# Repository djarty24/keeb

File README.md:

# Keeb Journal
Hack Club Keeb custom keyboard.

## Table of Contents
* [6/8](#68)

## 6/8
Just found out about Hack Club Keeb! I wanted to get started with this challenge.

### Planning Your Keyboard
I first read through the [Planning Your Keyboard](https://keeb.hackclub.com/docs/planning/) section in the docs and started brainstorming what I wanted my keyboard to look like. After doing some research, I've decided on a 75% layout for my Mac. I want it to look pretty standard, like this image:

The personalization will be through the keycaps! I'll also add fun illustrations on the PCB silkscreen. I'm thinking of designing my own Monet themed keycaps or purchasing custom ones off of Etsy like the following:

As for the case, I want it to have slight borders around everything and larger borders to separate the arrow keys and function row like the first image displayed.

```
Esc   F1 F2 F3 F4   F5 F6 F7 F8   F9 F10 F11 F12   Power

`  1  2  3  4  5  6  7  8  9  0  -  =   Backspace     Home
Tab Q  W  E  R  T  Y  U  I  O  P  [  ]   \          PgUp
Caps A  S  D  F  G  H  J  K  L  ;  '   Return       PgDn
Shift Z  X  C  V  B  N  M  ,  .  /   Shift   ↑      End
Ctrl Opt Cmd        Space        Cmd Opt     ← ↓ →
```

Design Time: ~90 min

### Designing the PCB (day 1)
Next, I moved on to the [Desighing the PCB](https://keeb.hackclub.com/docs/pcb-design/) section in the docs.

I've decided on linear switches since they seem to be the quietest and best for wrist health.

Initially I was pretty confused with how to even get started. So I headed over to YouTube and watched a tutorial by [Joe Scotto](https://www.youtube.com/watch?v=7LyziNdFlew) that explained direct vs. matrix wiring. Looking at my reference image, my keyboard needs 15 columns and 6 rows, which means my microcontroller needs at least 21 pins. This fits perfectly within the Raspberry Pi Pico's 26 GPIO pins!

Now, it was time to open up KiCAD and get started.

In the tutorial, it said I would need stabilizers for keys larger than 2u. So what I did next was identify the size of each key. Most keys were 1u, however some exceptions:

Tab: 1.5u
Caps Lock: 1.75u
Left Shift: 2.25u
Right Shift: 1.75u
Backslash: 1.5u
Return: 2.25u
Backspace: 2u
Space: 6.25u
Ctrl/Opt/Cmd/Right Cmd/1.25u

My eyes hurt really bad after squinting over the reference image but I believe this is right. So, the only keys that I need stabilizers for are Left Shift, Return, Backspace, and Space.

Then I created one row of keys.

## 6/9

Today, I continued working on the PCB. I finished up adding all of the key-diode units and orienting them to match my physical keyboard inspo. Although it isn't perfectly aligned it should be good enough to move on to the next step. Here's what my matrix looked like:

Next, I added in the Pico and added labels to its GPIO pins. I also added the stabilizers and 5 mounting holes as well.

Now, it was time to move on to the next step!

### Designing the PCB (day 2)

THIS TOOK ME 8 HOURS. I don't have many screenshots since I was pretty locked in but I had to manually orient every single switch-diode unit to match the exact layout I wanted. The grid system in KiCad is pretty bad, so I calculated all of the X-Y coordinates of all 81 keys using a formula I made on Desmos and positioned them accordingly. Then, I placed the diodes and routed all of my traces. This is what it looks like now:

The orientation of stuff is a little ugly but I'm not too picky about how it will look as long as it functions. In the future I will most probably remake this with a different MCU that's more compact than the Pico. This is what the 3d view looks like:

I went to GrabCAD and downloaded some 3D models of the Cherry MX keycaps and switches that were 1u. However, I got tired of adding them all in because I couldn't find a way to globally update their footprints to link to the model, so I added enough to just get an idea of what it would look like. I also added in a 1.5u stabilizer to test how that would look.

Final step for this part was running the Design Rules Checker (DRC) to make sure everything was good. I cleaned up some connections, ran the DRC again, and the PCB was ready to go! I also committed and pushed all of this to GitHub.

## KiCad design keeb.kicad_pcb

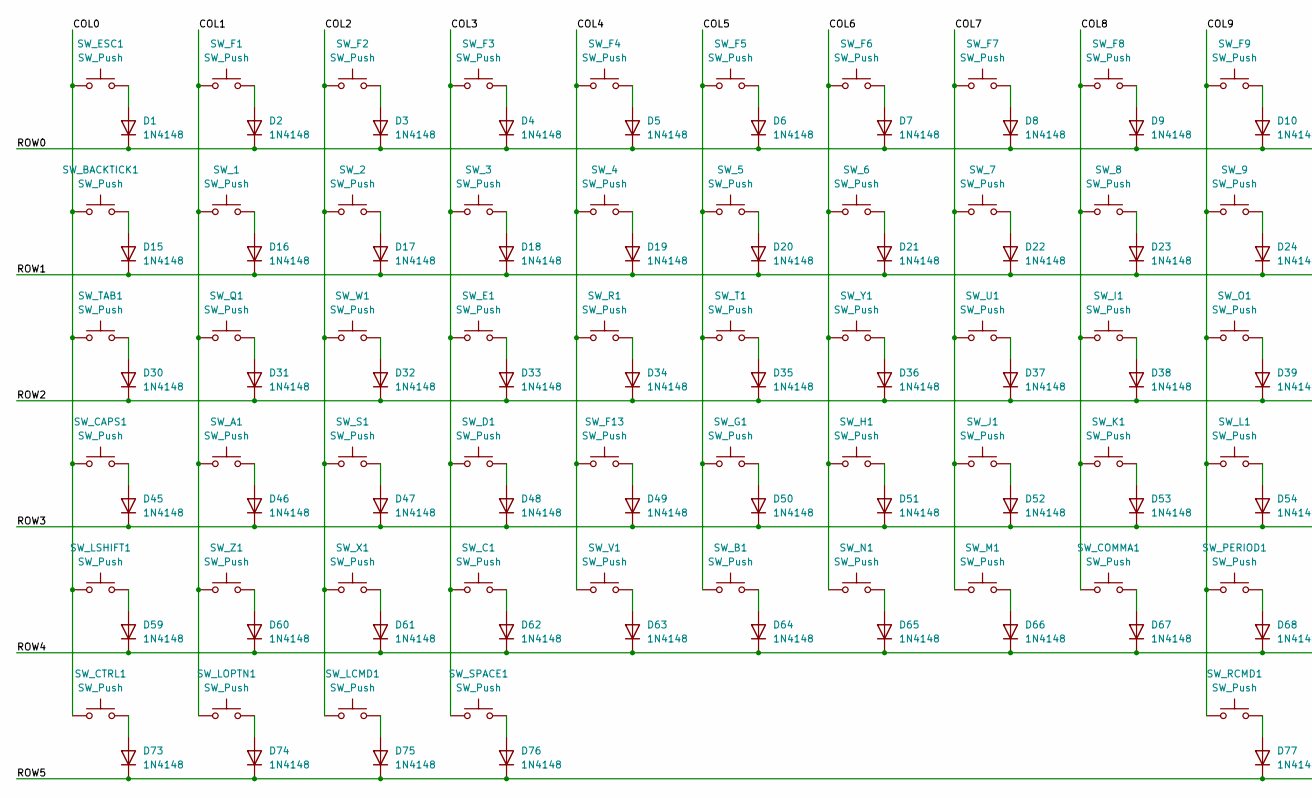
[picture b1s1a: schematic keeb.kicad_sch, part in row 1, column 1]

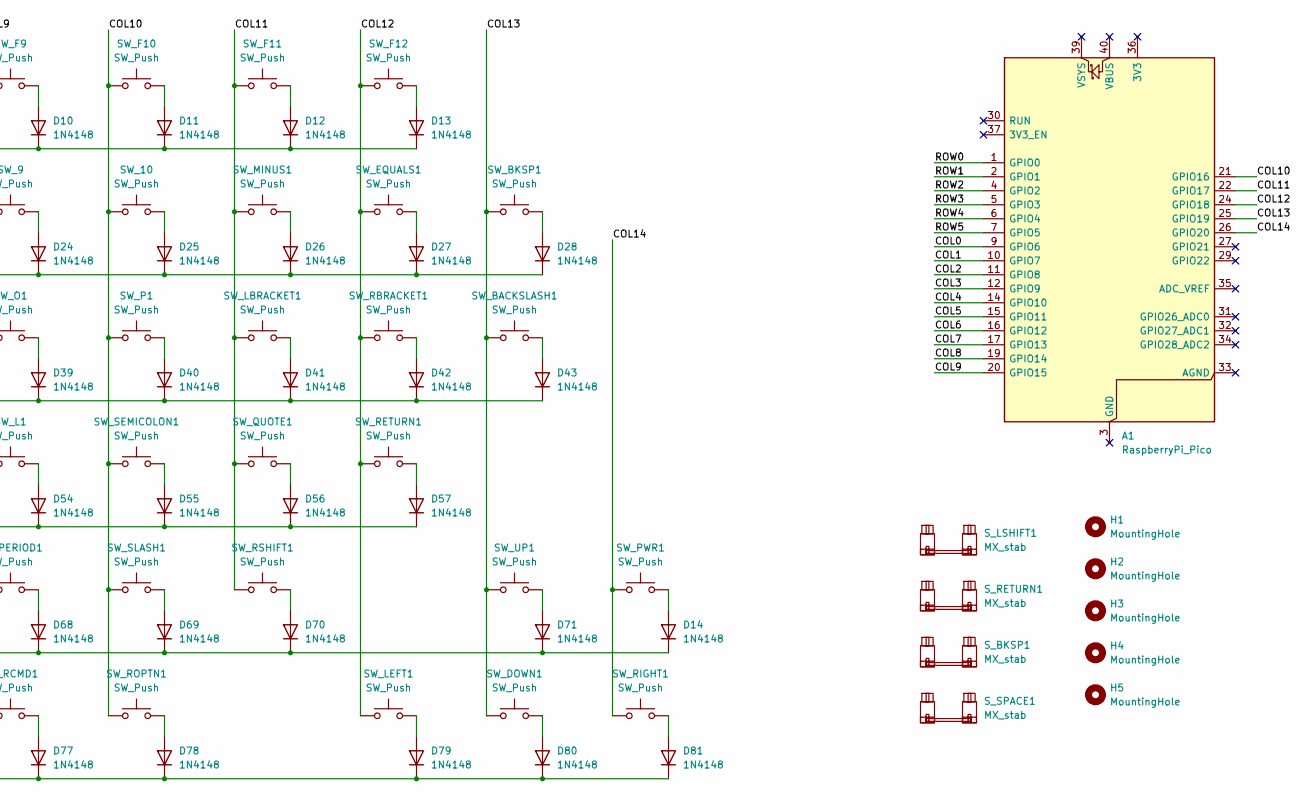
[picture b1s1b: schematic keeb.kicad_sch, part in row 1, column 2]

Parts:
A1: RaspberryPi_Pico; RaspberryPi_Pico_Common_THT
D1, D2, D3, D4, D5, D6, D7, D8, D9, D10, D11, D12, D13, D14, D15, D16, D17, D18, D19, D20, D21, D22, D23, D24, D25, D26, D27, D28, D30, D31, D32, D33, D34, D35, D36, D37, D38, D39, D40, D41, D42, D43, D45, D46, D47, D48, D49, D50, D51, D52, D53, D54, D55, D56, D57, D59, D60, D61, D62, D63, D64, D65, D66, D67, D68, D69, D70, D71, D73, D74, D75, D76, D77, D78, D79, D80, D81: 1N4148; D_DO-35_SOD27_P7.62mm_Horizontal
H1, H2, H3, H4, H5: MountingHole; MountingHole_2.2mm_M2
SW_1, SW_2, SW_3, SW_4, SW_5, SW_6, SW_7, SW_8, SW_9, SW_10: SW_Push; SW_MX_1u
SW_A1: SW_Push; SW_MX_1u
SW_B1: SW_Push; SW_MX_1u
SW_BACKSLASH1: SW_Push; SW_MX_1u
SW_BACKTICK1: SW_Push; SW_MX_1u
SW_BKSP1: SW_Push; SW_MX_1u
SW_C1: SW_Push; SW_MX_1u
SW_CAPS1: SW_Push; SW_MX_1u
SW_COMMA1: SW_Push; SW_MX_1u
SW_CTRL1: SW_Push; SW_MX_1u
SW_D1: SW_Push; SW_MX_1u
SW_DOWN1: SW_Push; SW_MX_1u
SW_E1: SW_Push; SW_MX_1u
SW_EQUALS1: SW_Push; SW_MX_1u
SW_ESC1: SW_Push; SW_MX_1u
SW_F1, SW_F2, SW_F3, SW_F4, SW_F5, SW_F6, SW_F7, SW_F8, SW_F9, SW_F10, SW_F11, SW_F12, SW_F13: SW_Push; SW_MX_1u
SW_G1: SW_Push; SW_MX_1u
SW_H1: SW_Push; SW_MX_1u
SW_I1: SW_Push; SW_MX_1u
SW_J1: SW_Push; SW_MX_1u
SW_K1: SW_Push; SW_MX_1u
SW_L1: SW_Push; SW_MX_1u
SW_LBRACKET1: SW_Push; SW_MX_1u
SW_LCMD1: SW_Push; SW_MX_1u
SW_LEFT1: SW_Push; SW_MX_1u
SW_LOPTN1: SW_Push; SW_MX_1u
SW_LSHIFT1: SW_Push; SW_MX_1u
SW_M1: SW_Push; SW_MX_1u
SW_MINUS1: SW_Push; SW_MX_1u
SW_N1: SW_Push; SW_MX_1u
SW_O1: SW_Push; SW_MX_1u
SW_P1: SW_Push; SW_MX_1u
SW_PERIOD1: SW_Push; SW_MX_1u
SW_PWR1: SW_Push; SW_MX_1u
SW_Q1: SW_Push; SW_MX_1u
SW_QUOTE1: SW_Push; SW_MX_1u
SW_R1: SW_Push; SW_MX_1u
SW_RBRACKET1: SW_Push; SW_MX_1u
SW_RCMD1: SW_Push; SW_MX_1u
SW_RETURN1: SW_Push; SW_MX_1u
SW_RIGHT1: SW_Push; SW_MX_1u
SW_ROPTN1: SW_Push; SW_MX_1u
SW_RSHIFT1: SW_Push; SW_MX_1u
SW_S1: SW_Push; SW_MX_1u
SW_SEMICOLON1: SW_Push; SW_MX_1u
SW_SLASH1: SW_Push; SW_MX_1u
SW_SPACE1: SW_Push; SW_MX_1u
SW_T1: SW_Push; SW_MX_1u
SW_TAB1: SW_Push; SW_MX_1u
SW_U1: SW_Push; SW_MX_1u
SW_UP1: SW_Push; SW_MX_1u
SW_V1: SW_Push; SW_MX_1u
SW_W1: SW_Push; SW_MX_1u
SW_X1: SW_Push; SW_MX_1u
SW_Y1: SW_Push; SW_MX_1u
SW_Z1: SW_Push; SW_MX_1u
S_BKSP1: MX_stab; STAB_MX_2u
S_LSHIFT1: MX_stab; STAB_MX_P_2.25u
S_RETURN1: MX_stab; STAB_MX_P_2.25u
S_SPACE1: MX_stab; STAB_MX_P_6.25u

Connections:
/COL0: A1.9 (GPIO6), SW_BACKTICK1.1, SW_CAPS1.1, SW_CTRL1.1, SW_ESC1.1, SW_LSHIFT1.1, SW_TAB1.1
/COL1: A1.10 (GPIO7), SW_1.1, SW_A1.1, SW_F1.1, SW_LOPTN1.1, SW_Q1.1, SW_Z1.1
/COL2: A1.11 (GPIO8), SW_2.1, SW_F2.1, SW_LCMD1.1, SW_S1.1, SW_W1.1, SW_X1.1
/COL3: A1.12 (GPIO9), SW_3.1, SW_C1.1, SW_D1.1, SW_E1.1, SW_F3.1, SW_SPACE1.1
/COL4: A1.14 (GPIO10), SW_4.1, SW_F4.1, SW_F13.1, SW_R1.1, SW_V1.1
/COL5: A1.15 (GPIO11), SW_5.1, SW_B1.1, SW_F5.1, SW_G1.1, SW_T1.1
/COL6: A1.16 (GPIO12), SW_6.1, SW_F6.1, SW_H1.1, SW_N1.1, SW_Y1.1
/COL7: A1.17 (GPIO13), SW_7.1, SW_F7.1, SW_J1.1, SW_M1.1, SW_U1.1
/COL8: A1.19 (GPIO14), SW_8.1, SW_COMMA1.1, SW_F8.1, SW_I1.1, SW_K1.1
/COL9: A1.20 (GPIO15), SW_9.1, SW_F9.1, SW_L1.1, SW_O1.1, SW_PERIOD1.1, SW_RCMD1.1
/COL10: A1.21 (GPIO16), SW_10.1, SW_F10.1, SW_P1.1, SW_ROPTN1.1, SW_SEMICOLON1.1, SW_SLASH1.1
/COL11: A1.22 (GPIO17), SW_F11.1, SW_LBRACKET1.1, SW_MINUS1.1, SW_QUOTE1.1, SW_RSHIFT1.1
/COL12: A1.24 (GPIO18), SW_EQUALS1.1, SW_F12.1, SW_LEFT1.1, SW_RBRACKET1.1, SW_RETURN1.1
/COL13: A1.25 (GPIO19), SW_BACKSLASH1.1, SW_BKSP1.1, SW_DOWN1.1, SW_UP1.1
/COL14: A1.26 (GPIO20), SW_PWR1.1, SW_RIGHT1.1
/ROW0: A1.1 (GPIO0), D1.1 (K), D2.1 (K), D3.1 (K), D4.1 (K), D5.1 (K), D6.1 (K), D7.1 (K), D8.1 (K), D9.1 (K), D10.1 (K), D11.1 (K), D12.1 (K), D13.1 (K)
/ROW1: A1.2 (GPIO1), D15.1 (K), D16.1 (K), D17.1 (K), D18.1 (K), D19.1 (K), D20.1 (K), D21.1 (K), D22.1 (K), D23.1 (K), D24.1 (K), D25.1 (K), D26.1 (K), D27.1 (K), D28.1 (K)
/ROW2: A1.4 (GPIO2), D30.1 (K), D31.1 (K), D32.1 (K), D33.1 (K), D34.1 (K), D35.1 (K), D36.1 (K), D37.1 (K), D38.1 (K), D39.1 (K), D40.1 (K), D41.1 (K), D42.1 (K), D43.1 (K)
/ROW3: A1.5 (GPIO3), D45.1 (K), D46.1 (K), D47.1 (K), D48.1 (K), D49.1 (K), D50.1 (K), D51.1 (K), D52.1 (K), D53.1 (K), D54.1 (K), D55.1 (K), D56.1 (K), D57.1 (K)
/ROW4: A1.6 (GPIO4), D14.1 (K), D59.1 (K), D60.1 (K), D61.1 (K), D62.1 (K), D63.1 (K), D64.1 (K), D65.1 (K), D66.1 (K), D67.1 (K), D68.1 (K), D69.1 (K), D70.1 (K), D71.1 (K)
/ROW5: A1.7 (GPIO5), D73.1 (K), D74.1 (K), D75.1 (K), D76.1 (K), D77.1 (K), D78.1 (K), D79.1 (K), D80.1 (K), D81.1 (K)
unnamed: D1.2 (A), SW_ESC1.2
unnamed: D2.2 (A), SW_F1.2
unnamed: D3.2 (A), SW_F2.2
unnamed: D4.2 (A), SW_F3.2
unnamed: D5.2 (A), SW_F4.2
unnamed: D6.2 (A), SW_F5.2
unnamed: D7.2 (A), SW_F6.2
unnamed: D8.2 (A), SW_F7.2
unnamed: D9.2 (A), SW_F8.2
unnamed: D10.2 (A), SW_F9.2
unnamed: D11.2 (A), SW_F10.2
unnamed: D12.2 (A), SW_F11.2
unnamed: D13.2 (A), SW_F12.2
unnamed: D14.2 (A), SW_PWR1.2
unnamed: D15.2 (A), SW_BACKTICK1.2
unnamed: D16.2 (A), SW_1.2
unnamed: D17.2 (A), SW_2.2
unnamed: D18.2 (A), SW_3.2
unnamed: D19.2 (A), SW_4.2
unnamed: D20.2 (A), SW_5.2
unnamed: D21.2 (A), SW_6.2
unnamed: D22.2 (A), SW_7.2
unnamed: D23.2 (A), SW_8.2
unnamed: D24.2 (A), SW_9.2
unnamed: D25.2 (A), SW_10.2
unnamed: D26.2 (A), SW_MINUS1.2
unnamed: D27.2 (A), SW_EQUALS1.2
unnamed: D28.2 (A), SW_BKSP1.2
unnamed: D30.2 (A), SW_TAB1.2
unnamed: D31.2 (A), SW_Q1.2
unnamed: D32.2 (A), SW_W1.2
unnamed: D33.2 (A), SW_E1.2
unnamed: D34.2 (A), SW_R1.2
unnamed: D35.2 (A), SW_T1.2
unnamed: D36.2 (A), SW_Y1.2
unnamed: D37.2 (A), SW_U1.2
unnamed: D38.2 (A), SW_I1.2
unnamed: D39.2 (A), SW_O1.2
unnamed: D40.2 (A), SW_P1.2
unnamed: D41.2 (A), SW_LBRACKET1.2
unnamed: D42.2 (A), SW_RBRACKET1.2
unnamed: D43.2 (A), SW_BACKSLASH1.2
unnamed: D45.2 (A), SW_CAPS1.2
unnamed: D46.2 (A), SW_A1.2
unnamed: D47.2 (A), SW_S1.2
unnamed: D48.2 (A), SW_D1.2
unnamed: D49.2 (A), SW_F13.2
unnamed: D50.2 (A), SW_G1.2
unnamed: D51.2 (A), SW_H1.2
unnamed: D52.2 (A), SW_J1.2
unnamed: D53.2 (A), SW_K1.2
unnamed: D54.2 (A), SW_L1.2
unnamed: D55.2 (A), SW_SEMICOLON1.2
unnamed: D56.2 (A), SW_QUOTE1.2
unnamed: D57.2 (A), SW_RETURN1.2
unnamed: D59.2 (A), SW_LSHIFT1.2
unnamed: D60.2 (A), SW_Z1.2
unnamed: D61.2 (A), SW_X1.2
unnamed: D62.2 (A), SW_C1.2
unnamed: D63.2 (A), SW_V1.2
unnamed: D64.2 (A), SW_B1.2
unnamed: D65.2 (A), SW_N1.2
unnamed: D66.2 (A), SW_M1.2
unnamed: D67.2 (A), SW_COMMA1.2
unnamed: D68.2 (A), SW_PERIOD1.2
unnamed: D69.2 (A), SW_SLASH1.2
unnamed: D70.2 (A), SW_RSHIFT1.2
unnamed: D71.2 (A), SW_UP1.2
unnamed: D73.2 (A), SW_CTRL1.2
unnamed: D74.2 (A), SW_LOPTN1.2
unnamed: D75.2 (A), SW_LCMD1.2
unnamed: D76.2 (A), SW_SPACE1.2
unnamed: D77.2 (A), SW_RCMD1.2
unnamed: D78.2 (A), SW_ROPTN1.2
unnamed: D79.2 (A), SW_LEFT1.2
unnamed: D80.2 (A), SW_DOWN1.2
unnamed: D81.2 (A), SW_RIGHT1.2

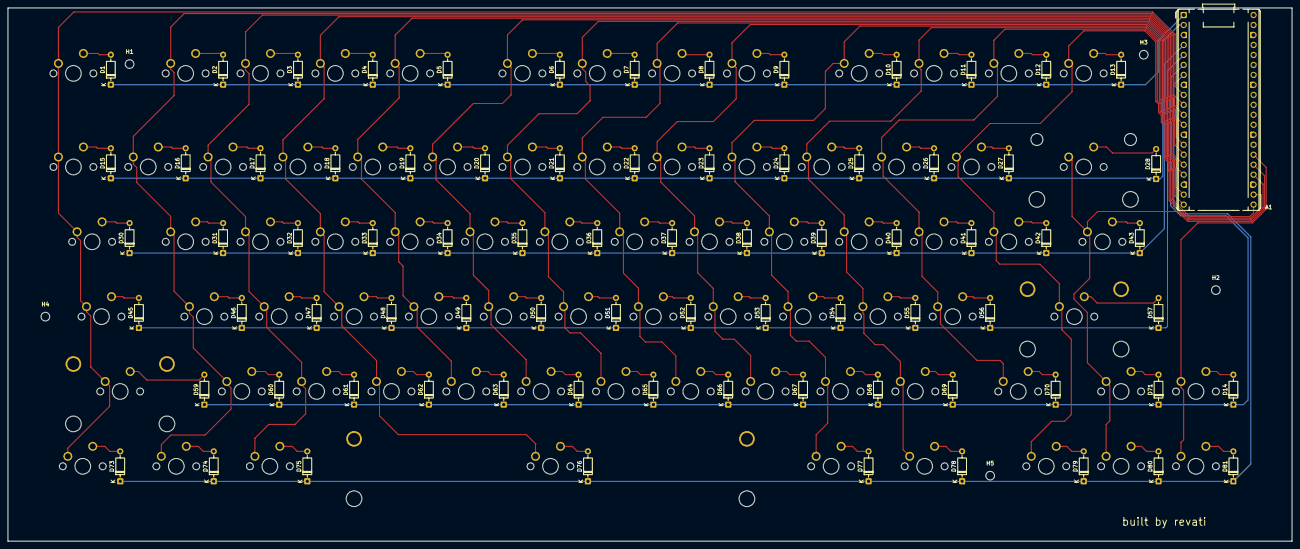
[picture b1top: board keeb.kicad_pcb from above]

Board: 2 copper layers, 326.9 x 135.7 mm, 164 parts (0 on the bottom side), 98 nets.

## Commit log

2026-06-10 kicad schematic & journal updates
